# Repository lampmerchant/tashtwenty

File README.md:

# TashTwenty

## Elevator Pitch

It's a DCD (the interface used by the Hard Disk 20 to plug in through the disk port) interface, contained entirely within a PIC16F1825 (14 pins, ~$1.84) or PIC16F1704 (14 pins, ~$1.39) microcontroller. It bit-bangs the low-level IWM protocol using the read/write and phase lines on the "DB"-19 disk port, no programmable logic devices of any kind required.

It interfaces to an MMC or compatible card and can emulate up to four DCD devices.  It also has an enable output which can be used to chain more DCD devices (though ROMs only support a maximum of four) and a floppy disk drive.

(Despite the name, there is nothing limiting it to 20 megabytes.)

## Project Status

Functional, though not rigorously tested.

## Caveats

Due to the dearth of documentation on the DCD protocol, the protocol only implements the commands whose formats are known, namely read, write, and device identification.  Responses to other commands are faked.  Fortunately, this seems to be enough for the device to function properly, including formatting.

The disk drive interface relies on use of the phase lines to read and write one-bit registers.  Because the PIC16F1825 firmware mimics the register set in code instead of programmable logic, it has a response time that is, in the worst case, approximately one microsecond.  This may interfere with the ability of faster Macs to detect it, though it is not known to do so at this point.  The PIC16F1704 firmware mimics the register set in logic and responds in effect instantly.

Certain Macs may have a limitation imposed by their ROM on the number of DCDs they support.  See [this link](https://github.com/lampmerchant/tashnotes/blob/main/macintosh/floppy/dcd/dcd.md) for details.

## PCBs and Products

* TashTwenty Tiny by [demik](https://github.com/demik)
   * [Files](https://github.com/lampmerchant/tashtwenty/tree/main/pcb/TashTwenty%20Tiny)
   * See latest release in this repository for gerbers
   * [Buy](https://ko-fi.com/s/2bfee029f5) from [CayMac Vintage](https://ko-fi.com/caymacvintage/shop)
   * Buy [PCBs](https://ko-fi.com/s/01a52bed98), [case panels](https://ko-fi.com/s/50199947e3), and [programmed PICs](https://ko-fi.com/s/2b28fb5562) from [Tashtari](https://ko-fi.com/tashtari/shop)
* TashTwenty Internal by [cheesestraws](https://github.com/cheesestraws)
   * [Files](https://github.com/lampmerchant/tashtwenty/tree/main/pcb/Internal)
   * See latest release in this repository for gerbers
* TashTwenty Rev 3 by [Tashtari](https://github.com/lampmerchant)
   * [Files](https://github.com/lampmerchant/tashtwenty/blob/main/pcb/tashtari-tashtwenty.brd)
   * See latest release in this repository for gerbers
* TashTwenty Budget Version by [CayMac Vintage](https://ko-fi.com/caymacvintage/shop)
   * [Buy](https://ko-fi.com/s/77f53b293e)
* TashTwenty Mega by [warmech](https://68kmla.org/bb/index.php?members/warmech.2497/)
   * Pending release
* TashTwenty Vertical by [hideehoo](https://68kmla.org/bb/index.php?members/hideehoo.4611/)
   * Pending release

## Technical Details

### Building Firmware

Building the firmware requires Microchip MPASM, which is included with their development environment, MPLAB.  Note that you **must** use MPLAB X version 5.35 or earlier or MPLAB 8 as later versions of MPLAB X have removed MPASM.

The firmware can also be built using gpasm, an MPASM-compatible assembler that is part of the [gputils](https://gputils.sourceforge.io/) project.  Please note, however, that the release builds are built using MPASM and compatibility with gpasm is not tested.

### MMC Card Format

The MMC card must have an MBR (Master Boot Record) aka DOS-type partition table with up to four primary partitions of type 0xAF (HFS).  Extended partitions are not supported.

#### Custom Icons

In the PIC16F1704 firmware, custom icons are supported using other values besides 0xAF for the partition type byte.  Other partition types besides 0xAF must be the number of a sector (for example, a partition of type 0x01 would point to the second sector) on the card formatted as follows:

* Bytes 0-255 must be the word "ICON" repeated 64 times.
* Bytes 256-383 must be a 32x32 icon, one bit per pixel, with '1' bits denoting black and '0' bits denoting white.
* Bytes 384-511 must be a 32x32 icon mask, one bit per pixel, with '1' bits denoting opaque and '0' bits denoting transparent.

If the sector is not in this format, the partition will be ignored, in order to safely support cards with non-HFS partitions.  Partitions of type 0xAF will always use the built-in icon and the hundred-seventy-sixth sector will not be checked for the format described above.

### DCD (Directly Connected Disks) Protocol

See [this link](https://github.com/lampmerchant/tashnotes/tree/main/macintosh/floppy/dcd) for details.

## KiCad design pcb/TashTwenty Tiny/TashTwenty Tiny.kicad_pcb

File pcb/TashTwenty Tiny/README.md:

# TashTwenty Tiny

This is a dual PCB design, using mostly through hole components (with the exeption of the SD connector). It's designed this way to be period correct and easy to build for people who don't like soldering SMT components

This folder contains the source KiKad files for the main board. Please check the DB19_IDC20 subfolder for the DB19 to IDC20 adapter. 

## BOM
### BOM (main board)
Here is the BOM for the main board. Part number are what was tested on prototypes board but you may find alternatives easily, especially resistors and sockets

| Reference(s)          | Value      | Quantity | Notes                                  | Part number           |
|-----------------------|------------|----------|----------------------------------------|-----------------------|
| C1, C2                | 2.2uF      | 2        | radial electrolytic capacitors 4x1.5mm | Jamicon SHR2R2M1HC07M |
| C3, C4                | 100nF      | 2        | ceramic capacitor 5.08mm               | Weltron 453358        |
| D1                    | Green      | 1        | 5mm green LED                          | Kingbright L-53SGD    |
| D2                    | Yellow+Red | 1        | 5mm dual color common cathode LED      | Kingbright L-59EYW    |
| J1                    | SD Card    | 1        | SD Card connector                      | TE 2041021-1          |
| J2                    | IDC20      | 1        | IDC 2x10 Header                        | BLK 10120560          |
| Q1                    | BC337      | 1        | NPN BJT Transistor                     | BC337                 |
| R10, R11              | 330Ω       | 2        | standard 0.25W carbon film resistor    | TRU TC-CFR0W4J0331    |
| R1, R3, R5, R8        | 1200Ω      | 4        | standard 0.25W carbon film resistor    | TRU TC-CFR0W4J0122    |
| R2, R4, R6            | 2200Ω      | 3        | standard 0.25W carbon film resistor    | TRU TC-CFR0W4J0222    |
| R7, R9, R12, R13, R14 | 10kΩ       | 5        | standard 0.25W carbon film resistor    | TRU TC-CFR0W4J0103    |
| U1                    | PIC16F1704 | 1        | PIC 8-bit Microcontroller (DIP-14)     | PIC16F1704-I/P        |
| U2                    | 74ACT08    | 1        | Quad TTL 2-Input AND Gate              | SN74ACT08N            |
| U3                    | 3.3V LDO   | 1        | 3.3V LDO voltage regulator             | MCP1700-3302E/TO      |

Optional

| Reference(s)          | Value      | Quantity | Notes                                  | Part number           |
|-----------------------|------------|----------|----------------------------------------|-----------------------|
| J1                    | -          | 1        | 1x2 header + jumper or wire            | -                     |
| U1, U2                | socket     | 2        | DIP-14 socket                          | TRU 14-LC-TT          |
| Case                  | ABS        | 1        | Instrument Case, ABS 2.6x2.6"          | HM 1593K(TBU\|GY\|BK) |

Using sockets is recommended because it will allow you to reclaim the gates and microcontroler if your board is broken. This will also allow you to upgrade the firmware if a future firmware is released.

Bridging J3 connects the !ENBL pin on the microcontroller to the !ENBL pin on the 2x20 header, which is what you want for the overwhelming majority of cases where you're connecting the board to an external/secondary floppy drive port that has !ENBL2 in the connector where it should be. It's fine to bridge the two pins with a piece of wire, but if you want this expandability available to you, it'd be better to solder a two-pin header and stick a jumper on it when not in use. The pin closest to the center of the board is the one connected to the microcontroller.

### BOM (adapter board)
This is a matching board for TashTwenty. Please use this one to avoid any damage to your computer or TashTwenty. Others adapters boards are wired differently

| Reference(s)          | Value      | Quantity | Notes                                  | Part number        |
|-----------------------|------------|----------|----------------------------------------|--------------------|
| J1                    | IDC20      | 1        | IDC 2x10 Header                        | BLK 10120560       |
| J2                    | DB19       | 1        | DB19 wire male connector               | Good luck.         |

### BOM (external links)
Here is a mouser link (without the case):
- https://www.mouser.fr/ProjectManager/ProjectDetail.aspx?AccessID=4e3ee30a16

Here us a digikey (without the case):
- https://www.digikey.com/short/n4d8tf04

### IDC cable
You need a cable to connect both boards
Any straight IDC-20 cable should work (pin 1 to pin 1, etc). Macintosh floppy cables are compatible. We used a few Apple cables for prototyping:
- Quadra 800 (Apple P/N 590-0862-B)
- PowerMac 7200-7600 (Apple P/N 590-4529-A)

If you are looking for a new one, a compatible assembly is made buy Advantech under the part number PCL-10120-1E.

## PCBs
the PCBs are simple 2 layers boards. The gerbers are avaible in the release section.
Check for the following files:
* TTT_12.zip: main board revision 1.2
* DB19_IDC20.zip: adapter board revision 1.0

You should be use any mainstream PCB manufacturer for theses. Nothing special about them. PCB thickness should FR-4 with a 1.6mm thickness
On JLCPCB, select "Specify a location" to the option "Remove Order Number"

## Building
Building is straightworfard. It's recommended to start with the SD Card connector, then components, and headers + sockets last.

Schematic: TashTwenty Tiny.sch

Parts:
C3: 100nF; C_Disc_D4.3mm_W1.9mm_P5.00mm
J1: SD_Card; SD_TE_2041021
R1, R3, R5: 1200; R_Axial_DIN0207_L6.3mm_D2.5mm_P7.62mm_Horizontal
R2, R4, R6: 2200; R_Axial_DIN0207_L6.3mm_D2.5mm_P7.62mm_Horizontal
R7, R14: 10k; R_Axial_DIN0207_L6.3mm_D2.5mm_P7.62mm_Horizontal
U1: PIC16F1825-IP; DIP-14_W7.62mm
U2: 74ACT08; DIP-14_W7.62mm

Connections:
+3V3: J1.4, R14.1; also elsewhere on the board
+5V: C3.2, R7.1, U1.1, U2.14; also elsewhere on the board
/MMC_MISO: U1.9, U2.11
/MMC_MISO_LV: J1.7, R14.2, U2.13
/MMC_MOSI: R5.1, U1.8
/MMC_MOSI_LV: J1.2, R5.2, R6.1
/MMC_SCK: R1.1, U1.10
/MMC_SCK_LV: J1.5, R1.2, R2.1
/~MMC_CS: R3.1, U1.7
/~MMC_CS_LV: J1.1, R3.2, R4.1
GND: C3.1, J1.3, J1.6, J1.12, R2.2, R4.2, R6.2, U1.14, U2.7; also elsewhere on the board
unnamed 14: U2.3; also elsewhere on the board
unnamed 17: U2.4, U2.5; also elsewhere on the board
unnamed: R7.2, U2.12
unnamed 20: U2.1, U2.9; also elsewhere on the board
unnamed 21: U2.6; also elsewhere on the board
unnamed 22: U2.8; also elsewhere on the board
PH0: U1.12; also elsewhere on the board
PH1: U1.11; also elsewhere on the board
PH2: U1.4; also elsewhere on the board
PH3: U1.3; also elsewhere on the board
RD: U1.6; also elsewhere on the board
WR: U1.5, U2.10; also elsewhere on the board
~ENABLE: U1.2, U2.2; also elsewhere on the board

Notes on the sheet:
IDC20 Connector
5V to 3.3V level converters
3.3V to 5V level converter
LEDs

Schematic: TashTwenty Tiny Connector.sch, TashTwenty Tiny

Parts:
C1, C2: 2.2uF; CP_Radial_D4.0mm_P1.50mm
C4: 100nF; C_Disc_D4.3mm_W1.9mm_P5.00mm
H1, H2, H3: M3; MountingHole_3.2mm_M3_Pad
J2: IDC20; IDC-Header_2x10_P2.54mm_Vertical
J3: Conn_01x02; PinHeader_1x02_P2.54mm_Vertical
U2: 74ACT08; DIP-14_W7.62mm
U3: MCP1700-3302E_TO92; TO-92_Inline

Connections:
+3V3: C1.1, U3.3; also elsewhere on the board
+5V: C2.1, C4.1, J2.11, U2.14, U3.2; also elsewhere on the board
+12V: J2.13, J2.15, J2.17, J2.19; also elsewhere on the board
/MMC_MISO: U2.11; also elsewhere on the board
/MMC_MISO_LV: U2.13; also elsewhere on the board
GND: C1.2, C2.2, C4.2, J2.1, J2.3, J2.5, J2.7, U2.7, U3.1; also elsewhere on the board
unnamed 14: U2.3; also elsewhere on the board
unnamed: J2.14, J3.1
unnamed 17: U2.4, U2.5; also elsewhere on the board
unnamed 19: U2.12; also elsewhere on the board
unnamed 20: U2.1, U2.9; also elsewhere on the board
unnamed 21: U2.6; also elsewhere on the board
unnamed 22: U2.8; also elsewhere on the board
PH0: J2.2; also elsewhere on the board
PH1: J2.4; also elsewhere on the board
PH2: J2.6; also elsewhere on the board
PH3: J2.8; also elsewhere on the board
RD: J2.16; also elsewhere on the board
WR: J2.18, U2.10; also elsewhere on the board
~ENABLE: J3.2, U2.2; also elsewhere on the board

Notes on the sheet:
Mounting holes

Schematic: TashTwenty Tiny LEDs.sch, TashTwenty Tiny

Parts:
D1: LED; LED_D5.0mm_Horizontal_O3.81mm_Z3.0mm
D2: LED_Dual_ACA; LED_D5.0mm-3_Horizontal_O3.81mm_Z3.0mm
Q1: BC337; TO-92_Inline
R8: 1200; R_Axial_DIN0207_L6.3mm_D2.5mm_P7.62mm_Horizontal
R9, R12, R13: 10k; R_Axial_DIN0207_L6.3mm_D2.5mm_P7.62mm_Horizontal
R10, R11: 330; R_Axial_DIN0207_L6.3mm_D2.5mm_P7.62mm_Horizontal
U2: 74ACT08; DIP-14_W7.62mm

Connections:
+5V: R9.1, R13.1, U2.14; also elsewhere on the board
+12V: R8.1; also elsewhere on the board
/MMC_MISO: U2.11; also elsewhere on the board
/MMC_MISO_LV: U2.13; also elsewhere on the board
GND: D1.1, Q1.3, U2.7; also elsewhere on the board
unnamed: D1.2, R8.2
unnamed: D2.1, R11.1
unnamed: D2.2, U2.3
unnamed: D2.3, R10.1
unnamed: Q1.1, R13.2, U2.4, U2.5
unnamed: Q1.2, R12.1
unnamed 19: U2.12; also elsewhere on the board
unnamed: R9.2, U2.1, U2.9
unnamed: R10.2, U2.6
unnamed: R11.2, U2.8
RD: R12.2; also elsewhere on the board
WR: U2.10; also elsewhere on the board
~ENABLE: U2.2; also elsewhere on the board

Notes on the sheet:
This gate will sink the led when /ENABLE is low. Read is /ENABLE low AND RD low Write is /ENABLE low and WR high

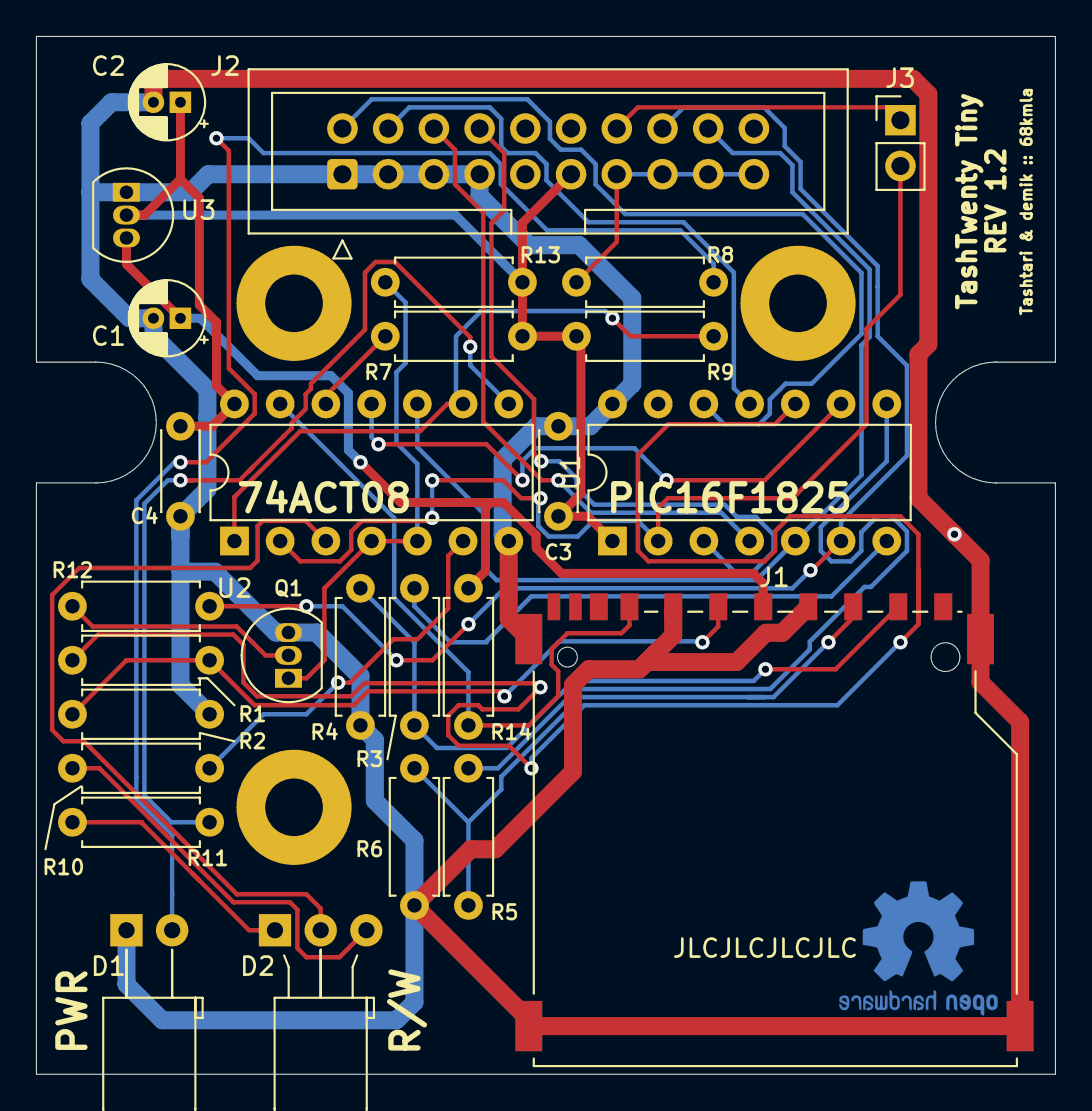
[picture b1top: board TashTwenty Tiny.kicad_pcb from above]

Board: 2 copper layers, 56.6 x 57.7 mm, 30 parts (0 on the bottom side), 30 nets.

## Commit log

2021-11-03 20211103
2021-11-06 20211106
2021-11-14 20211114
2021-11-20 20211120
2021-11-23 20211122
2021-11-26 20211126
2021-11-26 add board rev 1
2021-11-26 update README to mention use of MBR
2021-11-28 20211128
2022-03-17 initial relase of the TashTwentt Tiny PCB: a dual PCB THT implementation of TashTwenty
2022-03-18 added TTT adapter board
2022-03-18 added small readme and BOM
2022-03-19 added mouser basket link
2022-03-19 update README.md with compatibility information
2022-03-20 added librairy for DB19
2022-03-20 added GitHub, 68kmla URLs and revisions to source files
2022-03-21 added info about BOMs, mouser basket, etc…
2022-03-21 added info for IDC-20 cable
2022-03-24 Updated mouser basket link
2022-04-01 fixed typo (J1 -> J3)
2022-04-01 Basket update + more J3 documentation
2022-04-10 update README with new info about compatibility
2022-04-14 update README.md with new info about number of DCDs
2022-04-21 20220421
2022-04-22 update README.md with particulars of PIC16F1704 firmware
2022-04-24 20220424
2022-05-01 1825/IIcx compatibility demonstrated
2022-05-01 add system software compatibility table
2022-05-10 added PCB Front Panel
2022-05-10 refreshed Mouser Basket
2022-05-10 added Ribbon Cable P/N
2022-05-11 added digikey basket
2022-05-17 added back panel PCB
2022-05-20 added missing TTT_BP.kicad_pcb
2022-05-21 PCB board rev 1.1: fixed R2 silkscreen
2022-06-04 20220604
2022-06-06 Switched PIC P/N to PIC16F1704
2022-06-06 updates mouser basket to 20220606
2022-06-06 PCB board rev 1.2: fix LED positions
2022-06-07 Rev 1.1 Front Panel: align LED and SD holes
2022-06-11 20220611
2022-06-22 20220621
2022-10-14 translate DCD document from MacDex
2022-10-14 missed translating a header from wiki markup
2022-12-01 note removal of MPASM from MPLAB X
2023-02-21 move DCD documentation to tashnotes
2024-02-28 Internal
2024-02-28 remove gerbers (they go in release)
2024-02-28 add list of PCBs/products to README
2024-04-04 fix Tashtari link
2024-05-28 add FUNDING.yml with ko-fi
2026-05-30 mention gputils as potential build tool
